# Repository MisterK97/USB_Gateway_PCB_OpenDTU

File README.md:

# USB-Gateway-Platine für z.B. OpenDTU auf ESP32-Basis

In diesem Repo werden die Unterlagen und Dateien zum USB-Gateway abgelegt.

Die Platine wurde mit Eagle entworfen und auf Basis des Schaltplans der Github-Page von OpenDTU (<https://github.com/tbnobody/OpenDTU>) erstellt.
Mit der besonderen Form der Platine kann das Gateway direkt über ein USB-Netzteil versorgt werden und benötigt daher kein Kabel oder eine zusätzliche Befestigung.

Wenn man die Platine fertigt gelötet hat und den ESP32 mit OpenDTU geflasht hat, müssen keine zusätzlichen Einstellungen bezüglich der GPIOs vorgenommen werden.
Die Pin-Belegung entspricht der Standardbelegung von OpenDTU.

**Schaltplan-Ausschnitt und Layout:**

**Benötigte Komponenten:**
- USB-Platine (siehe Dateien)
- ESP32 D1 MINI (<https://www.azdelivery.de/products/esp32-d1-mini>)
- NRF24L01 (<https://www.azdelivery.de/products/3x-nrf24l01-mit-2-4-ghz>)

Diese Repo hat nichts mit der OpenDTU-Repo (<https://github.com/tbnobody/OpenDTU>) zu tun und steht in keiner Absprache mit den Entwickler*innen. Danke für die tolle Arbeit der Community! Ich hoffe meine kleine Platine hilft euch!

Die Verwendung der gezeigten Platine bzw. des Schaltplanes erfolgt auf eigenes Risiko und ohne jegliche Gewährleistung!

Viel Spaß beim Modifizieren und Basteln! :)

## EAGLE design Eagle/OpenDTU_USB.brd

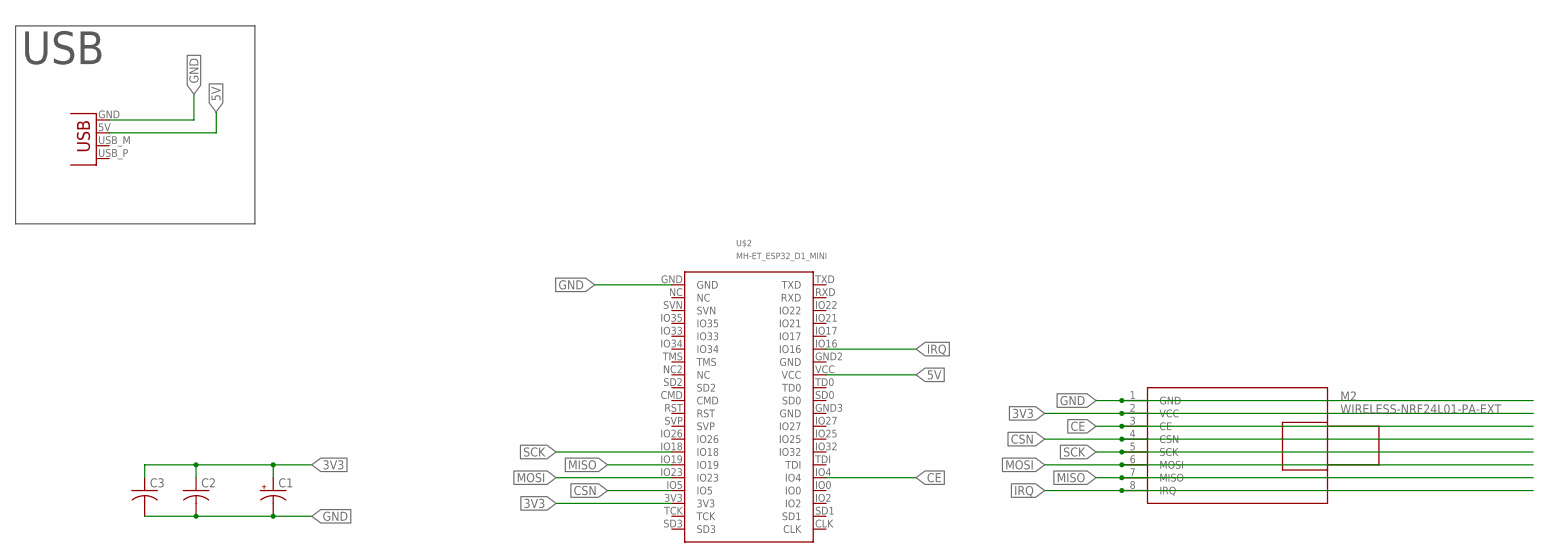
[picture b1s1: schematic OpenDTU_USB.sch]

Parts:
C1: CPOL-USE2.5-6; E2,5-6
C2, C3: C-USC0805K; C0805K
M2: WIRELESS-NRF24L01-PA-EXT
U$2: MH-ET_ESP32_D1_MINI
X1: USBPCB; USB-A-PCB

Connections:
3V3: C1.+, C2.1, C3.1, M2.2 (VCC), U$2.3V3
5V: U$2.VCC, X1.5V (VBUS)
CE: M2.3 (CE), U$2.IO4
CSN: M2.4 (CSN), U$2.IO5
GND: C1.-, C2.2, C3.2, M2.1 (GND), U$2.GND, X1.GND
IRQ: M2.8 (IRQ), U$2.IO16
MISO: M2.7 (MISO), U$2.IO19
MOSI: M2.6 (MOSI), U$2.IO23
SCK: M2.5 (SCK), U$2.IO18

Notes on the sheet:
USB

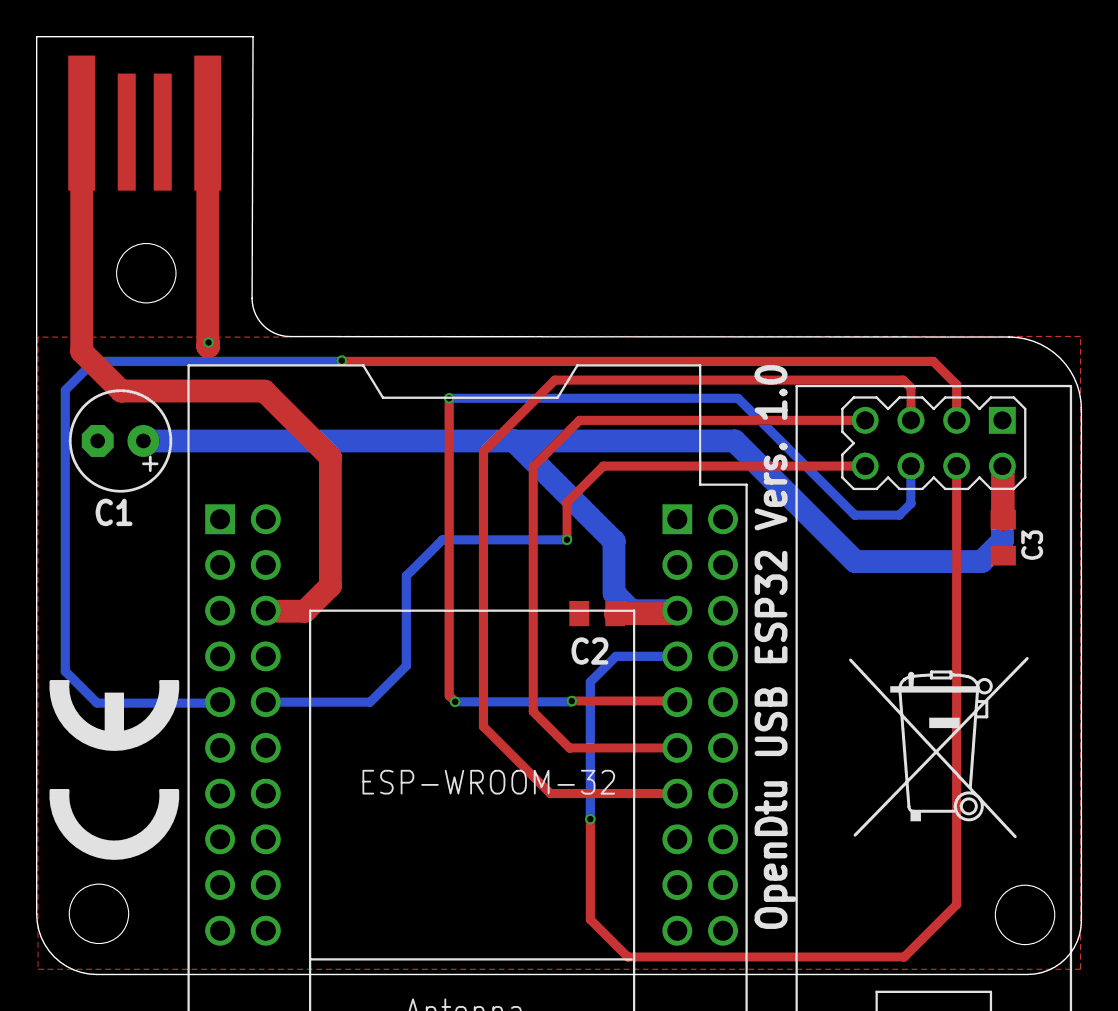
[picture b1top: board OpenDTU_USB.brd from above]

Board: 2 copper layers, 58.0 x 52.1 mm, 8 parts (0 on the bottom side), 9 nets.

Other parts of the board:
U$1: CE_7.3MM
U$3: MUELLTONNE_10.00

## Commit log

2023-04-09 Bilder hinzugefuegt
2023-04-09 readme updated
2023-04-09 bilder hinzugefügt
2023-08-08 Bilder und Schaltplan erneuert
2023-08-08 Bilder erneuert
2023-08-08 readme fix
2023-10-06 Schraubklemme hinzugefügt, Empfang verbessert, USB wegbrechbar

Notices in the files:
parts and their libraries:
SparkFun_Old: Licensing: CC v3.0 Share-Alike You are welcome to use this library for commercial purposes.
diy-modules: Released under the Creative Commons Attribution 4.0 International License: http://creativecommons.org/licenses/by/4.0
